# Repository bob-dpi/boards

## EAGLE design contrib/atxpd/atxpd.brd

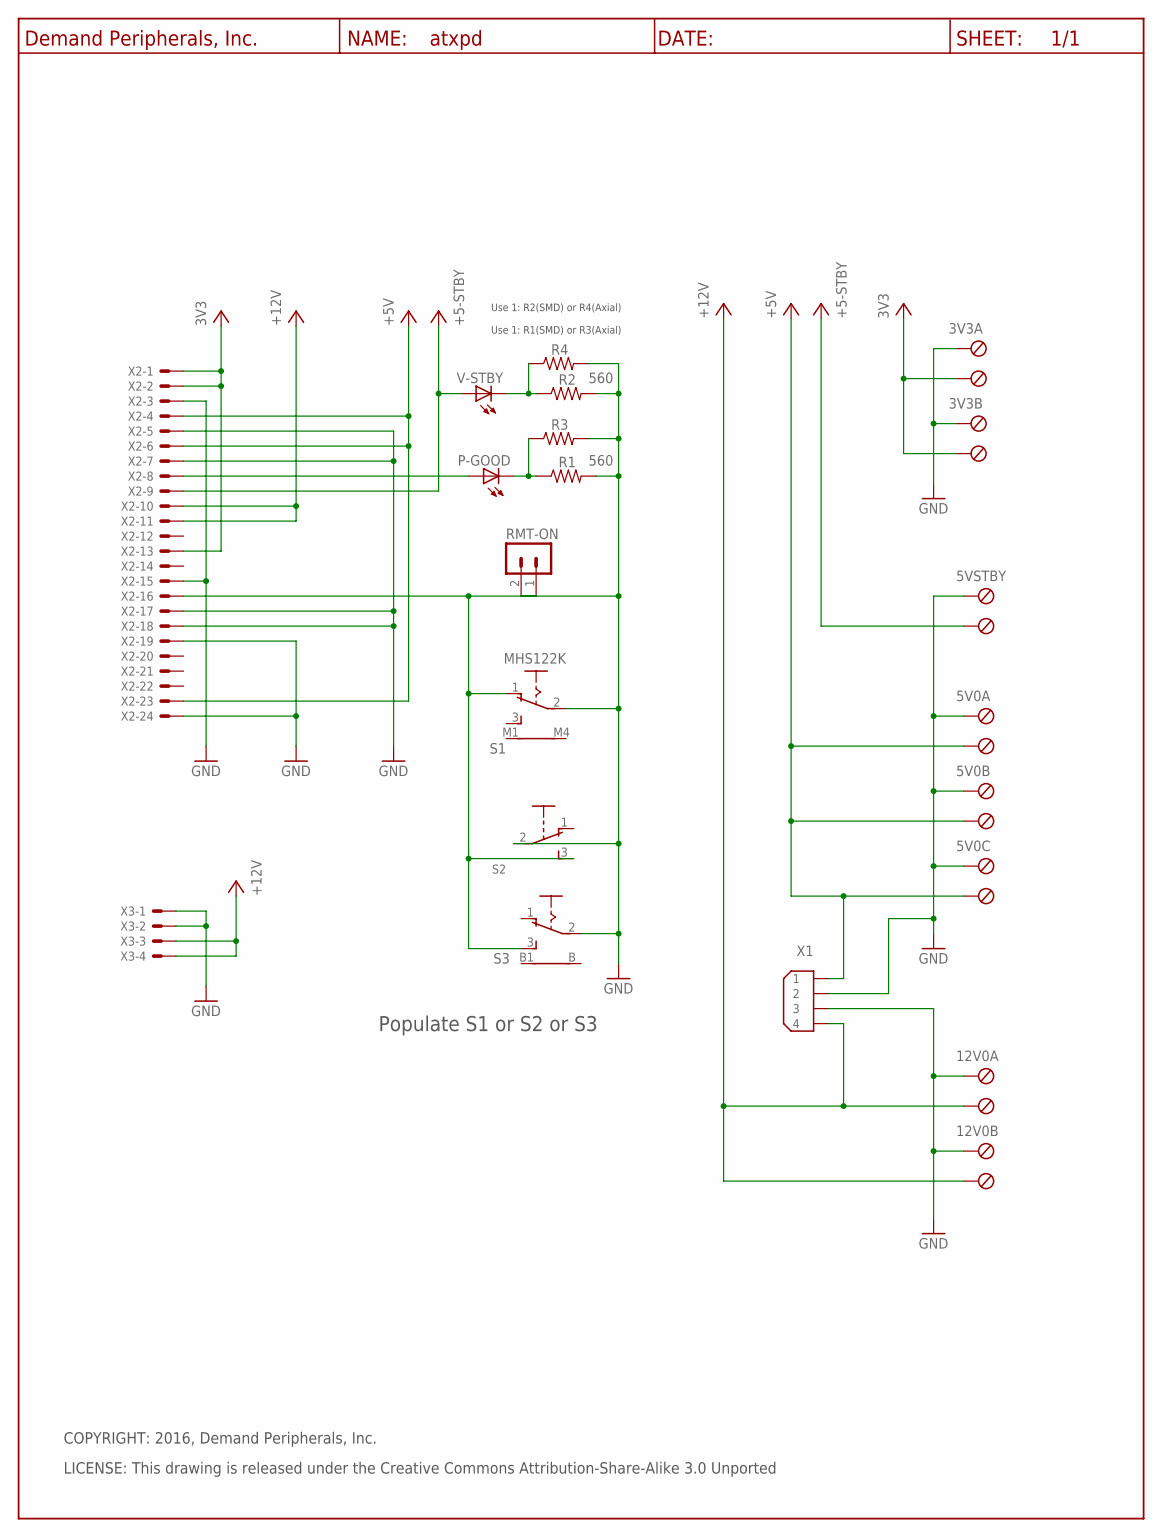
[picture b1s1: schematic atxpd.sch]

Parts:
3V3A, 3V3B, 5V0A, 5V0B, 5V0C, 5VSTBY, 12V0A, 12V0B: TBLK-5.08-X2
P-GOOD: 3mm_LED; LED5MM
R1, R2: 560; R0603
R3, R4: 560; R4TENTHS
RMT-ON: PinHdr254-2; HDR-2X1
S1: MHS122K
S2: TINYTOGGLE-SPDT-TH; SPDT-TENTHINCH
S3: Vert_SW(Option); TOGGLE_SPDT_PC
U$1: DP_FRAME_P; LETTER_P
V-STBY: 3mm_LED; LED5MM
X1: 9090-4V
X2: ATX_Std; 5566-24MOD
X3: ATX_Plus4; 5566-4MOD

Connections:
+3,3V: 3V3A.2 (KL1), 3V3B.2 (KL1), X2.1, X2.2, X2.13
+5V: 5V0A.2 (KL1), 5V0B.2 (KL1), 5V0C.2 (KL1), X1.1, X2.4, X2.6, X2.23
+5V/1: 5VSTBY.2 (KL1), V-STBY.A, X2.9
+5V/2: 12V0A.2 (KL1), 12V0B.2 (KL1), X1.4, X2.10, X2.11, X3.3, X3.4
GND: 3V3A.1 (KL), 3V3B.1 (KL), 5V0A.1 (KL), 5V0B.1 (KL), 5V0C.1 (KL), 5VSTBY.1 (KL), 12V0A.1 (KL), 12V0B.1 (KL), R1.2, R2.2, R3.2, R4.2, RMT-ON.2 (1), S1.2, S2.2, S3.2, X1.2, X1.3, X2.3, X2.5, X2.7, X2.15, X2.17, X2.18, X2.19, X2.24, X3.1, X3.2
unnamed: P-GOOD.A, X2.8
unnamed: P-GOOD.C, R1.1, R3.1
unnamed: R2.1, R4.1, V-STBY.C
unnamed: RMT-ON.1 (2), S1.1 (O), S2.3, S3.3 (S), X2.16

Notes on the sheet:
Use 1: R2(SMD) or R4(Axial)
Use 1: R1(SMD) or R3(Axial)
Populate S1 or S2 or S3
LICENSE: This drawing is released under the Creative Commons Attribution-Share-Alike 3.0 Unported
COPYRIGHT: 2016, Demand Peripherals, Inc.

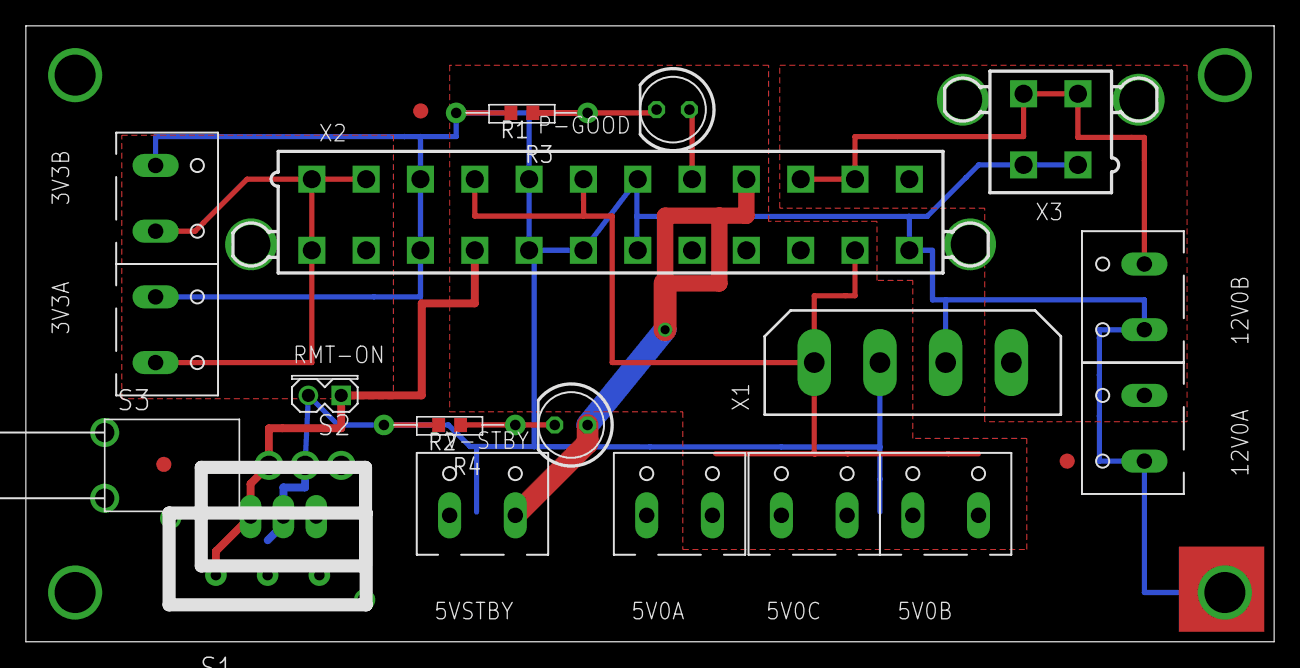
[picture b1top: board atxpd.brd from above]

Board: 2 copper layers, 96.5 x 47.6 mm, 25 parts (0 on the bottom side), 9 nets.

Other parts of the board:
U$9, U$10, U$11: FIDUCIAL

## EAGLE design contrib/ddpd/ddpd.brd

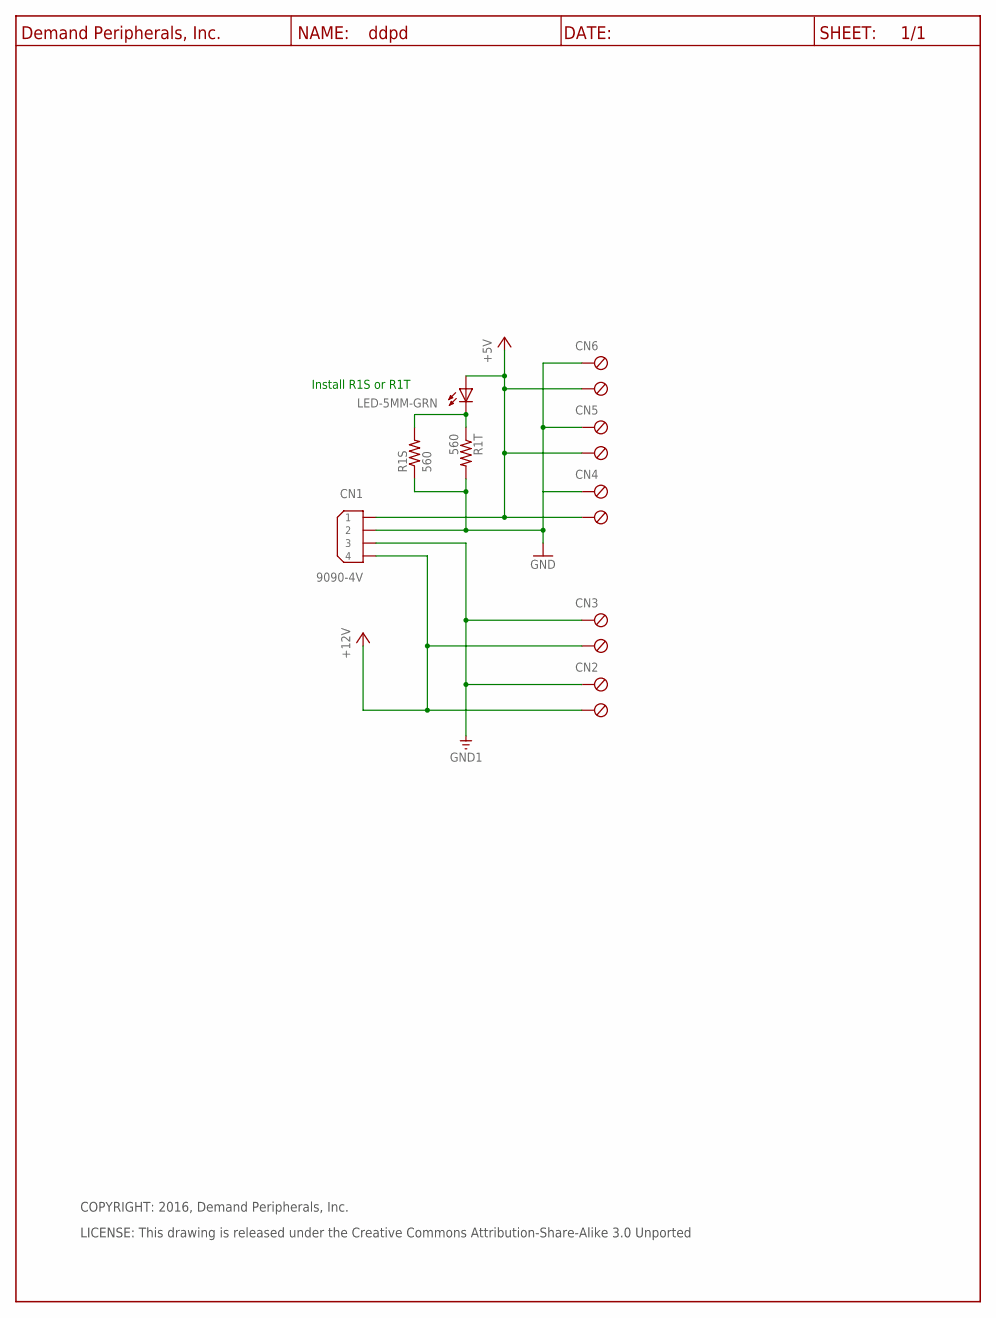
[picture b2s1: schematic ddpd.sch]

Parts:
+5V: LED-5MM-GRN; LED5MM
CN1: 9090-4V; 9090-4R
CN2, CN3, CN4, CN5, CN6: TBLK-5.08-X2
R1S: 560; R0603
R1T: 560; R4TENTHS
U$4: DP_FRAME_P; LETTER_P

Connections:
+5V: +5V.A, CN1.1, CN4.2 (KL1), CN5.2 (KL1), CN6.2 (KL1)
+5V/2: CN1.4, CN2.2 (KL1), CN3.2 (KL1)
GND: CN1.2, CN4.1 (KL), CN5.1 (KL), CN6.1 (KL), R1S.1, R1T.2
GND1: CN1.3, CN2.1 (KL), CN3.1 (KL)
unnamed: +5V.C, R1S.2, R1T.1

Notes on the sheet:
Install R1S or R1T
LICENSE: This drawing is released under the Creative Commons Attribution-Share-Alike 3.0 Unported
COPYRIGHT: 2016, Demand Peripherals, Inc.

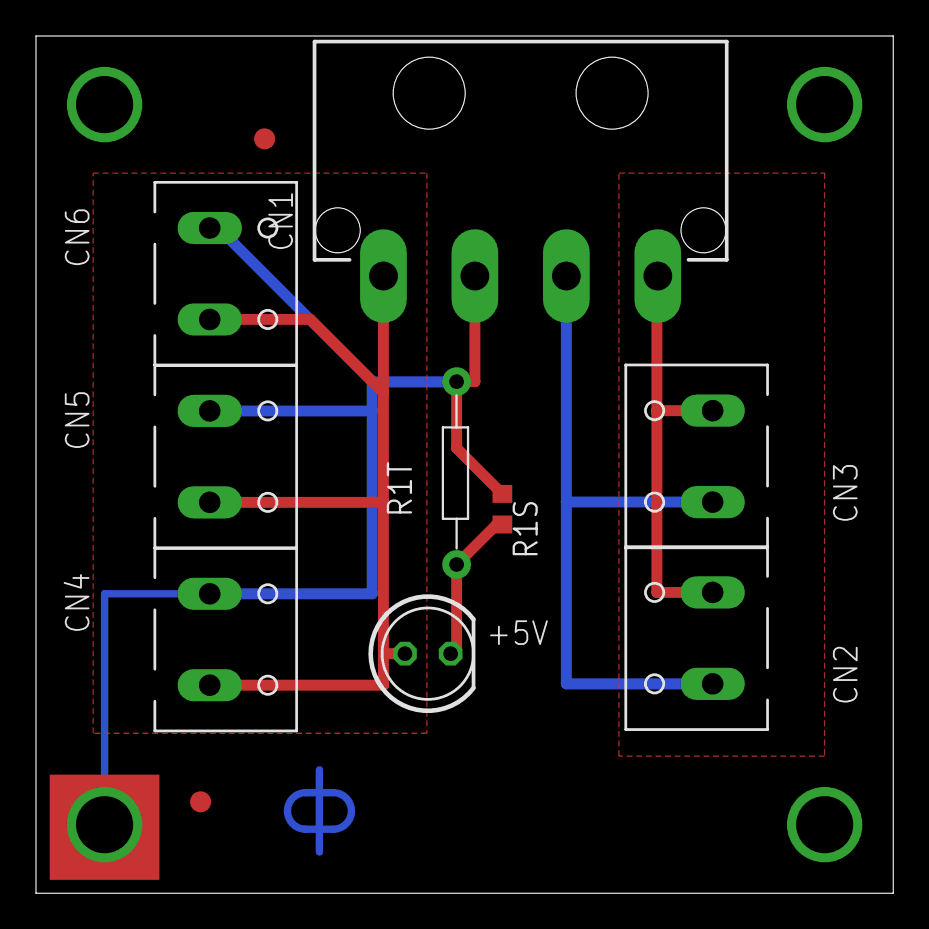
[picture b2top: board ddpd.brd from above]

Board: 2 copper layers, 47.6 x 47.6 mm, 13 parts (1 on the bottom side), 5 nets.

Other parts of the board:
U$1: DPI-1
U$2, U$3: FIDUCIAL

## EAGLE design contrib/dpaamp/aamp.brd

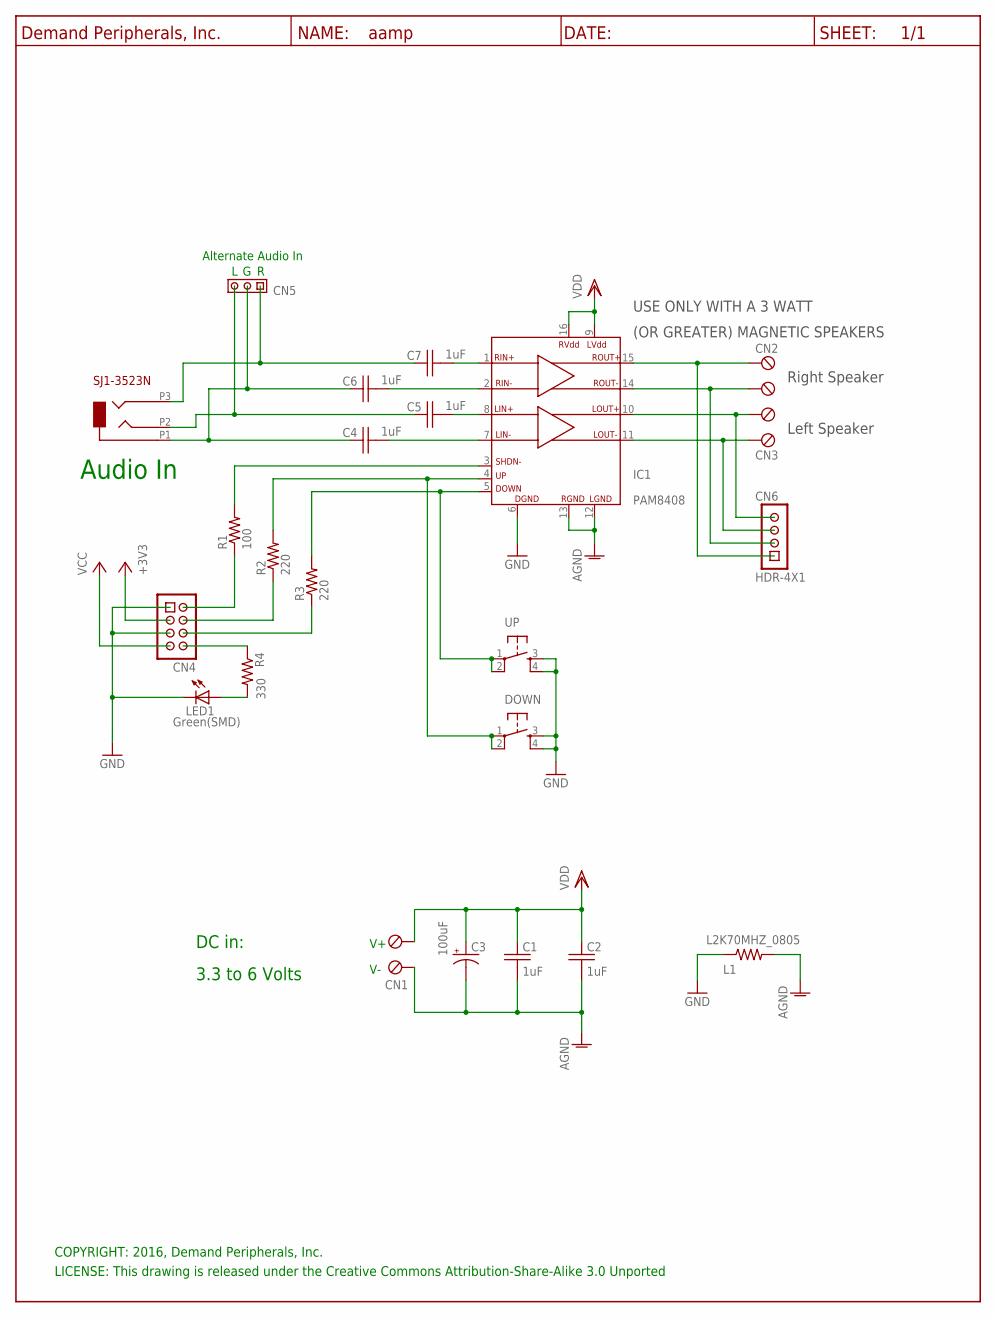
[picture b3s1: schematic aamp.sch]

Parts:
AUDIN: SJ1-3523N; CUI-SJ1-3523N
C1, C2, C4, C5, C6, C7: 1uF; C0603
C3: 100uF; E3.5-8
CN1, CN2, CN3: TBLK-5.08-X2
CN4: HDR-4X2-SHR; HDR-4X2
CN5: HDR-3X1
CN6: HDR-4X1
DOWN: DTSM-6
FRM1: DP_FRAME_P; P_FRAME
IC1: PAM8408; SO16
L1: L2K70MHZ_0805; R0805
LED1: Green(SMD); 0603
R1: 100; R0603
R2, R3: 220; R0603
R4: 330; R0603
UP: DTSM-6

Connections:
+3,3V: CN4.3
AGND: C1.2, C2.2, C3.-, CN1.1 (KL), IC1.12 (LGND), IC1.13 (RGND), L1.2
GND: CN4.1, CN4.5, DOWN.3, DOWN.4, IC1.6 (GND), L1.1, LED1.C, UP.3, UP.4
unnamed: AUDIN.P1 (1), C4.1, C6.1, CN5.2
unnamed: AUDIN.P2 (2), C5.1, CN5.3
unnamed: AUDIN.P3 (3), C7.1, CN5.1
unnamed: C7.2, IC1.1 (RIN+)
unnamed: CN4.8, R4.1
unnamed: C6.2, IC1.2 (RIN-)
unnamed: C5.2, IC1.8 (LIN+)
unnamed: C4.2, IC1.7 (LIN-)
unnamed: CN4.6, R3.1
unnamed: CN4.4, R2.1
unnamed: CN4.2, R1.1
unnamed: IC1.3 (SHDN-), R1.2
unnamed: LED1.A, R4.2
unnamed: DOWN.1, DOWN.2, IC1.4 (UP), R2.2
unnamed: IC1.5 (DOWN), R3.2, UP.1, UP.2
unnamed: CN3.2 (KL1), CN6.3, IC1.11 (LOUT-)
unnamed: CN3.1 (KL), CN6.4, IC1.10 (LOUT+)
unnamed: CN2.1 (KL), CN6.2, IC1.14 (ROUT-)
unnamed: CN2.2 (KL1), CN6.1, IC1.15 (ROUT+)
VCC: CN4.7
VDD: C1.1, C2.1, C3.+, CN1.2 (KL1), IC1.9 (LVDD), IC1.16 (RVDD)

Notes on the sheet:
DC in:
Audio In
3.3 to 6 Volts
USE ONLY WITH A 3 WATT
(OR GREATER) MAGNETIC SPEAKERS
COPYRIGHT: 2016, Demand Peripherals, Inc.
LICENSE: This drawing is released under the Creative Commons Attribution-Share-Alike 3.0 Unported
Left Speaker
Right Speaker
Alternate Audio In

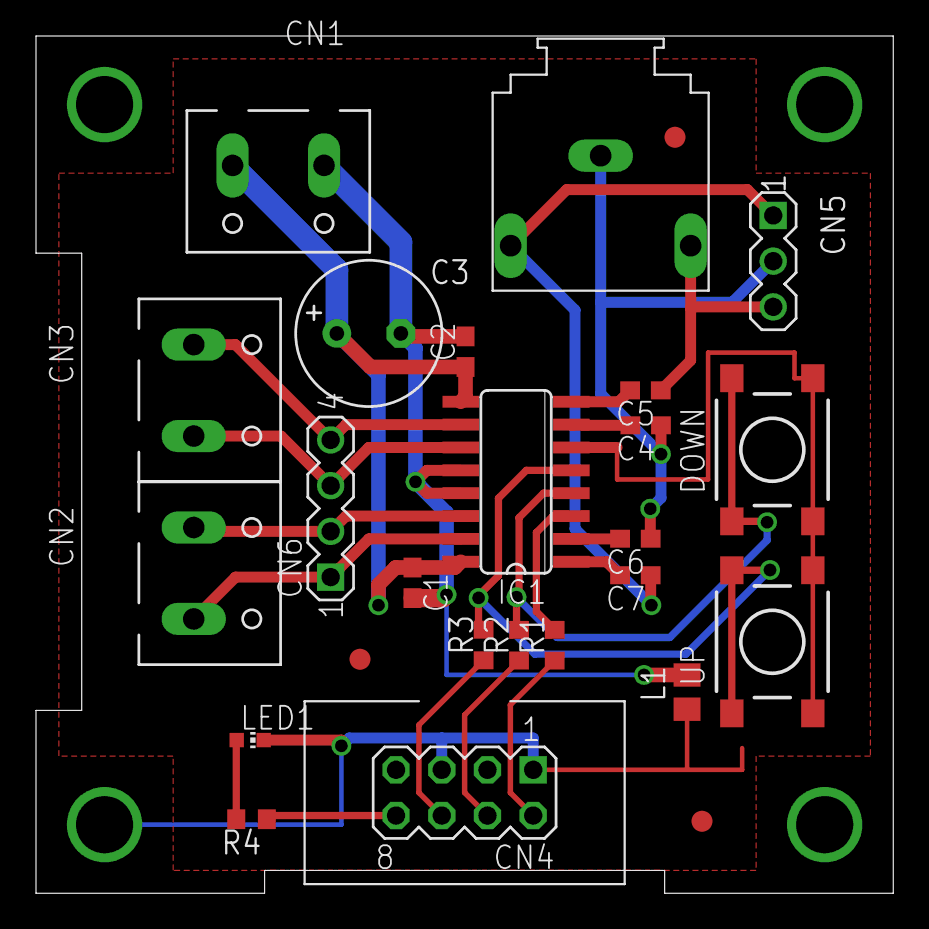
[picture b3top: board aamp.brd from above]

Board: 2 copper layers, 47.6 x 47.6 mm, 28 parts (1 on the bottom side), 22 nets.

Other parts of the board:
U$1: DPI-2
U$3, U$4, U$6: FIDUCIAL

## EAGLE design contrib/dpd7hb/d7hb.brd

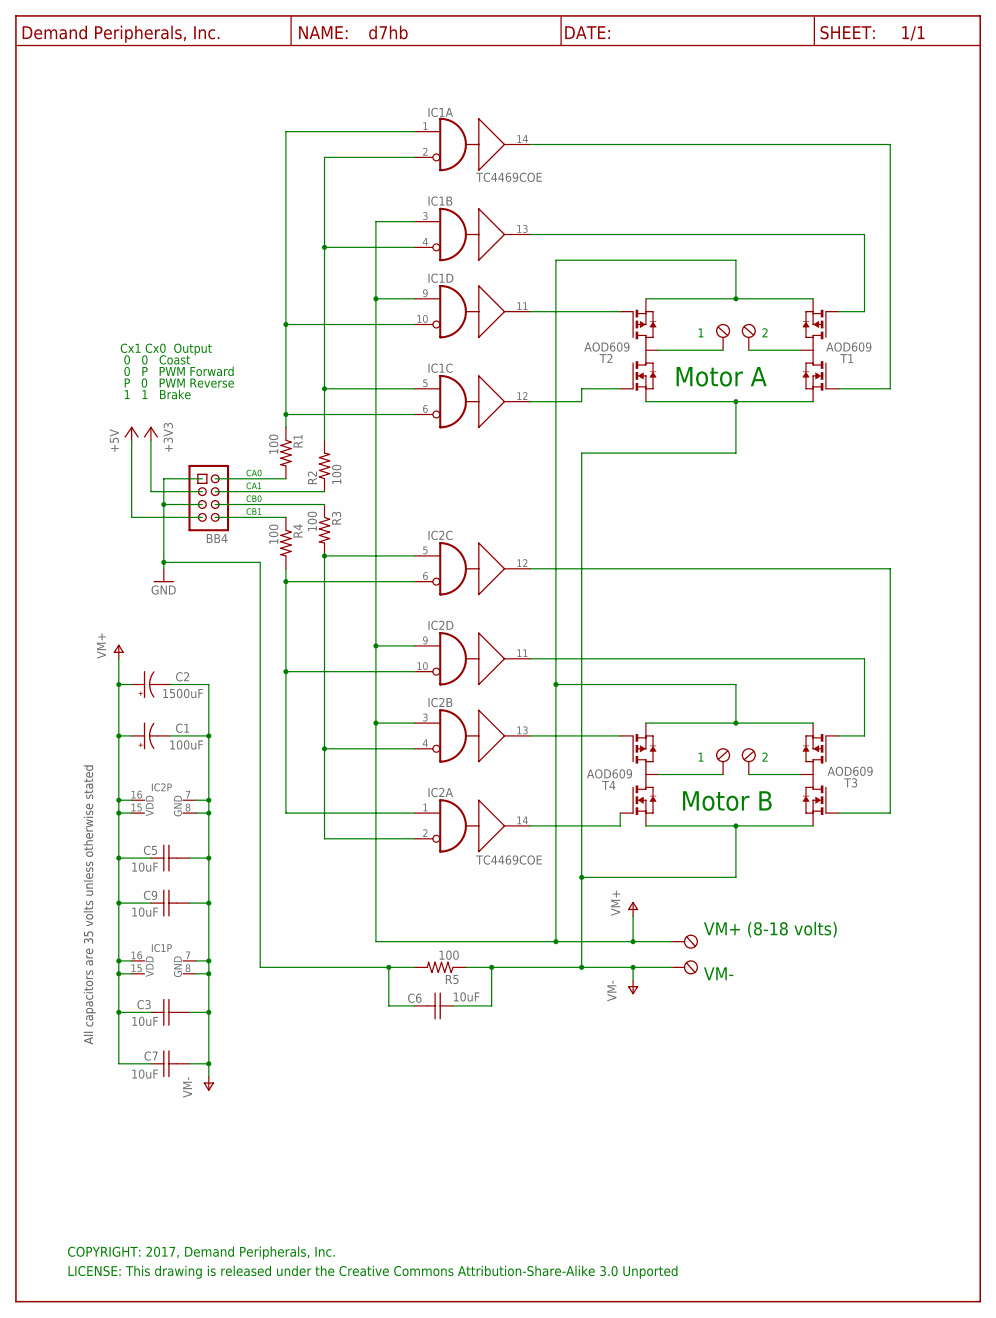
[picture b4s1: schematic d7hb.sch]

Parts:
BB4: BB_CON; HDR-4X2
C1: 100uF; E3.5-8
C2: 1500uF; E7,5-16
C3, C5, C6, C7, C9: 10uF; C0805
CN1, CN2, CN3: OSTTC022162; TBLK-5.08-X2
IC1, IC2: TC4469COE; SO-16DW
R1, R2, R3, R4, R5: 100; R0603
T1, T2, T3, T4: AOD609; TO252-41
U$1: DP_FRAME_P; LETTER_P

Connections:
+3V3: BB4.3
GND: BB4.1, BB4.5, C6.2, R5.2
unnamed: IC1.12 (Y), T2.2 (G1N)
unnamed: IC1.11 (Y), T2.5 (G2P)
unnamed: IC1.13 (Y), T1.5 (G2P)
unnamed: IC1.14 (Y), T1.2 (G1N)
unnamed: IC2.13 (Y), T4.5 (G2P)
unnamed: BB4.8, R4.1
unnamed: IC2.14 (Y), T4.2 (G1N)
unnamed: IC2.11 (Y), T3.5 (G2P)
unnamed: BB4.2, R1.2
unnamed: IC2.12 (Y), T3.2 (G1N)
unnamed: BB4.4, R2.1
unnamed: IC1.1 (A), IC1.6 (B), IC1.10 (B), R1.1
unnamed: IC1.2 (B), IC1.4 (B), IC1.5 (A), R2.2
unnamed: BB4.6, R3.1
unnamed: IC2.1 (A), IC2.6 (B), IC2.10 (B), R4.2
unnamed: IC2.2 (B), IC2.4 (B), IC2.5 (A), R3.2
unnamed: CN3.1 (KL), T2.CASE (D12)
unnamed: CN3.2 (KL1), T1.CASE (D12)
unnamed: CN2.2 (KL1), T4.CASE (D12)
unnamed: CN2.1 (KL), T3.CASE (D12)
V+: C1.+, C2.+, C3.1, C5.1, C7.1, C9.1, CN1.2 (KL1), IC1.3 (A), IC1.9 (A), IC1.15 (VDD), IC1.16 (VDD), IC2.3 (A), IC2.9 (A), IC2.15 (VDD), IC2.16 (VDD), T1.4 (S2P), T2.4 (S2P), T3.4 (S2P), T4.4 (S2P)
V-: C1.-, C2.-, C3.2, C5.2, C6.1, C7.2, C9.2, CN1.1 (KL), IC1.7 (GND), IC1.8 (GND), IC2.7 (GND), IC2.8 (GND), R5.1, T1.1 (S1N), T2.1 (S1N), T3.1 (S1N), T4.1 (S1N)
VCC: BB4.7

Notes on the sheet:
Motor A
VM+ (8-18 volts)
VM-
Motor B
CA0
CA1
CB0
CB1
Cx1 Cx0 Output
0 0 Coast
0 P PWM Forward
P 0 PWM Reverse
1 1 Brake
All capacitors are 35 volts unless otherwise stated
COPYRIGHT: 2017, Demand Peripherals, Inc.
LICENSE: This drawing is released under the Creative Commons Attribution-Share-Alike 3.0 Unported

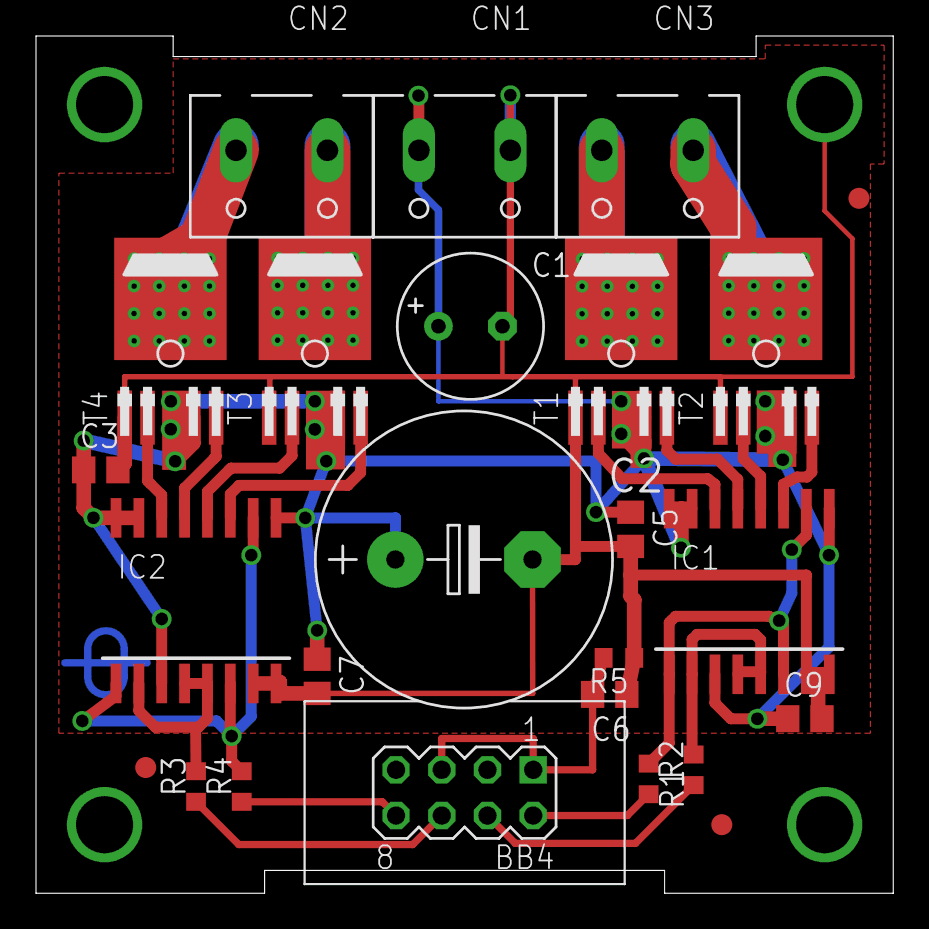
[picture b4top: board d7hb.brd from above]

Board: 2 copper layers, 47.6 x 47.6 mm, 27 parts (1 on the bottom side), 23 nets.

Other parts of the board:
U$2, U$3, U$4: FIDUCIAL
U$5: DPI-1

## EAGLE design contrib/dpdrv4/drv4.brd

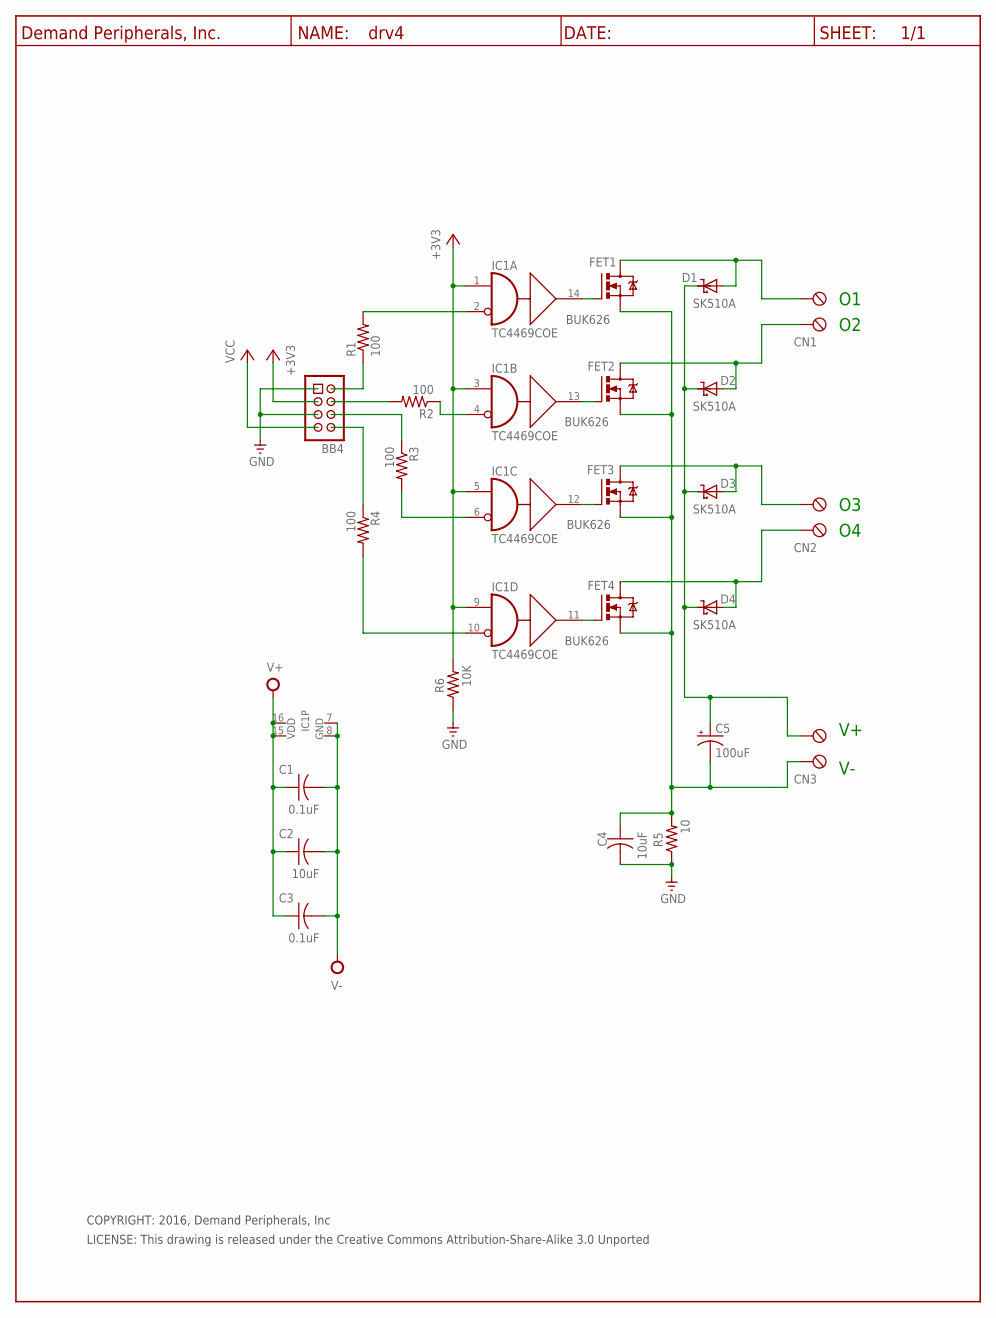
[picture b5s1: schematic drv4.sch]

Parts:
BB4: Keyed_Pin_Header_4x2(0.1"x0.1"); HDR-4X2
C1, C3: 0.1uF; C0603
C2, C4: 10uF; C0805
C5: 100uF; E3.5-8
CN1, CN2, CN3: TBLK-5.08-X2
D1, D2, D3, D4: SK510A; SMA
FET1, FET2, FET3, FET4: BUK626; DPACK_TO-252
IC1: TC4469COE; SO-16DW
R1, R2, R3, R4: 100; R0603
R5: 10; R0603
R6: 10K; R0603
U$1: DP_FRAME_P; P_FRAME

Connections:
+3V3: BB4.3, IC1.1 (A), IC1.3 (A), IC1.5 (A), IC1.9 (A), R6.2
GND: BB4.1, BB4.5, C4.2, R5.1, R6.1
unnamed: IC1.10 (B), R4.2
unnamed: IC1.2 (B), R1.2
unnamed: IC1.4 (B), R2.1
unnamed: FET1.1 (G), IC1.14 (Y)
unnamed: FET2.1 (G), IC1.13 (Y)
unnamed: FET3.1 (G), IC1.12 (Y)
unnamed: FET4.1 (G), IC1.11 (Y)
unnamed: BB4.2, R1.1
unnamed: BB4.4, R2.2
unnamed: BB4.6, R3.1
unnamed: IC1.6 (B), R3.2
unnamed: BB4.8, R4.1
O1: CN2.1 (KL), D4.A, FET4.4 (D)
O2: CN2.2 (KL1), D3.A, FET3.4 (D)
O3: CN1.1 (KL), D2.A, FET2.4 (D)
O4: CN1.2 (KL1), D1.A, FET1.4 (D)
V+: C1.1, C2.1, C3.1, C5.+, CN3.2 (KL1), D1.C (CC), D2.C (CC), D3.C (CC), D4.C (CC), IC1.15 (VDD), IC1.16 (VDD)
V-: C1.2, C2.2, C3.2, C4.1, C5.-, CN3.1 (KL), FET1.3 (S), FET2.3 (S), FET3.3 (S), FET4.3 (S), IC1.7 (GND), IC1.8 (GND), R5.2
VCC: BB4.7

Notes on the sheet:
COPYRIGHT: 2016, Demand Peripherals, Inc
LICENSE: This drawing is released under the Creative Commons Attribution-Share-Alike 3.0 Unported

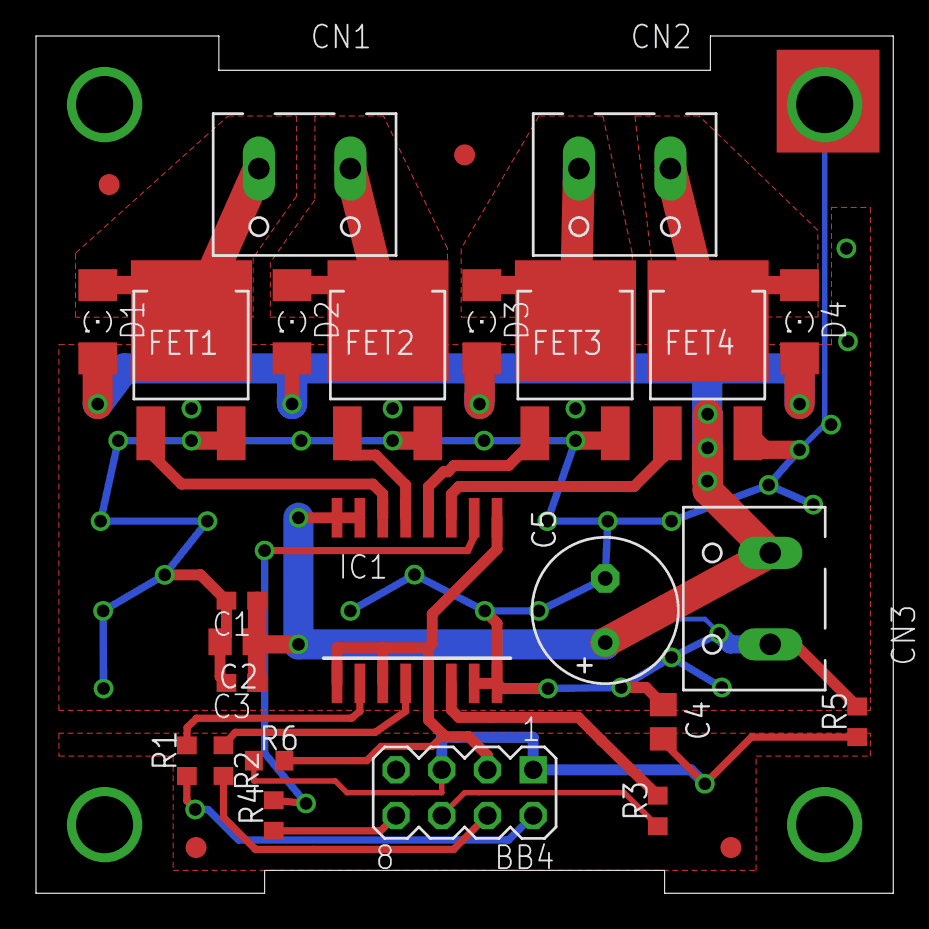
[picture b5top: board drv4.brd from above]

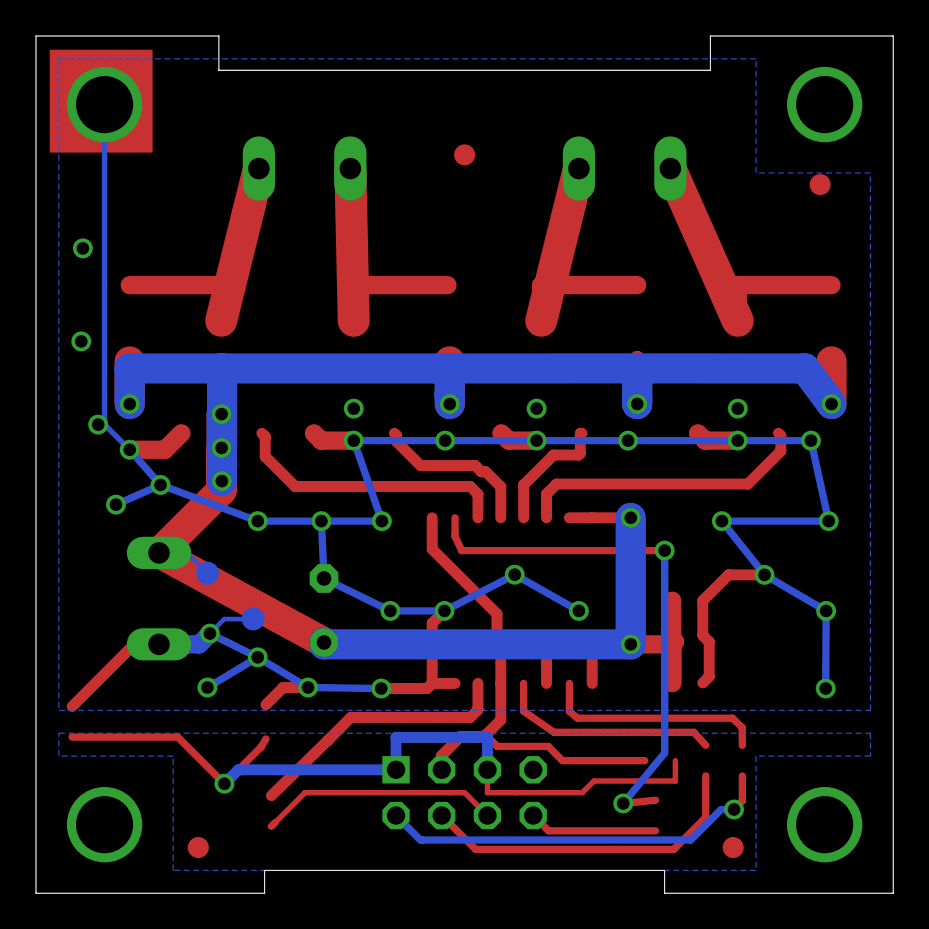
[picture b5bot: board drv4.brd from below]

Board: 2 copper layers, 47.6 x 47.6 mm, 32 parts (3 on the bottom side), 20 nets.

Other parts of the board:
E$6: TEST-POINT
U$2, U$3, U$4, U$5: FIDUCIAL
U$7: DPI-2
V-: TEST-POINT

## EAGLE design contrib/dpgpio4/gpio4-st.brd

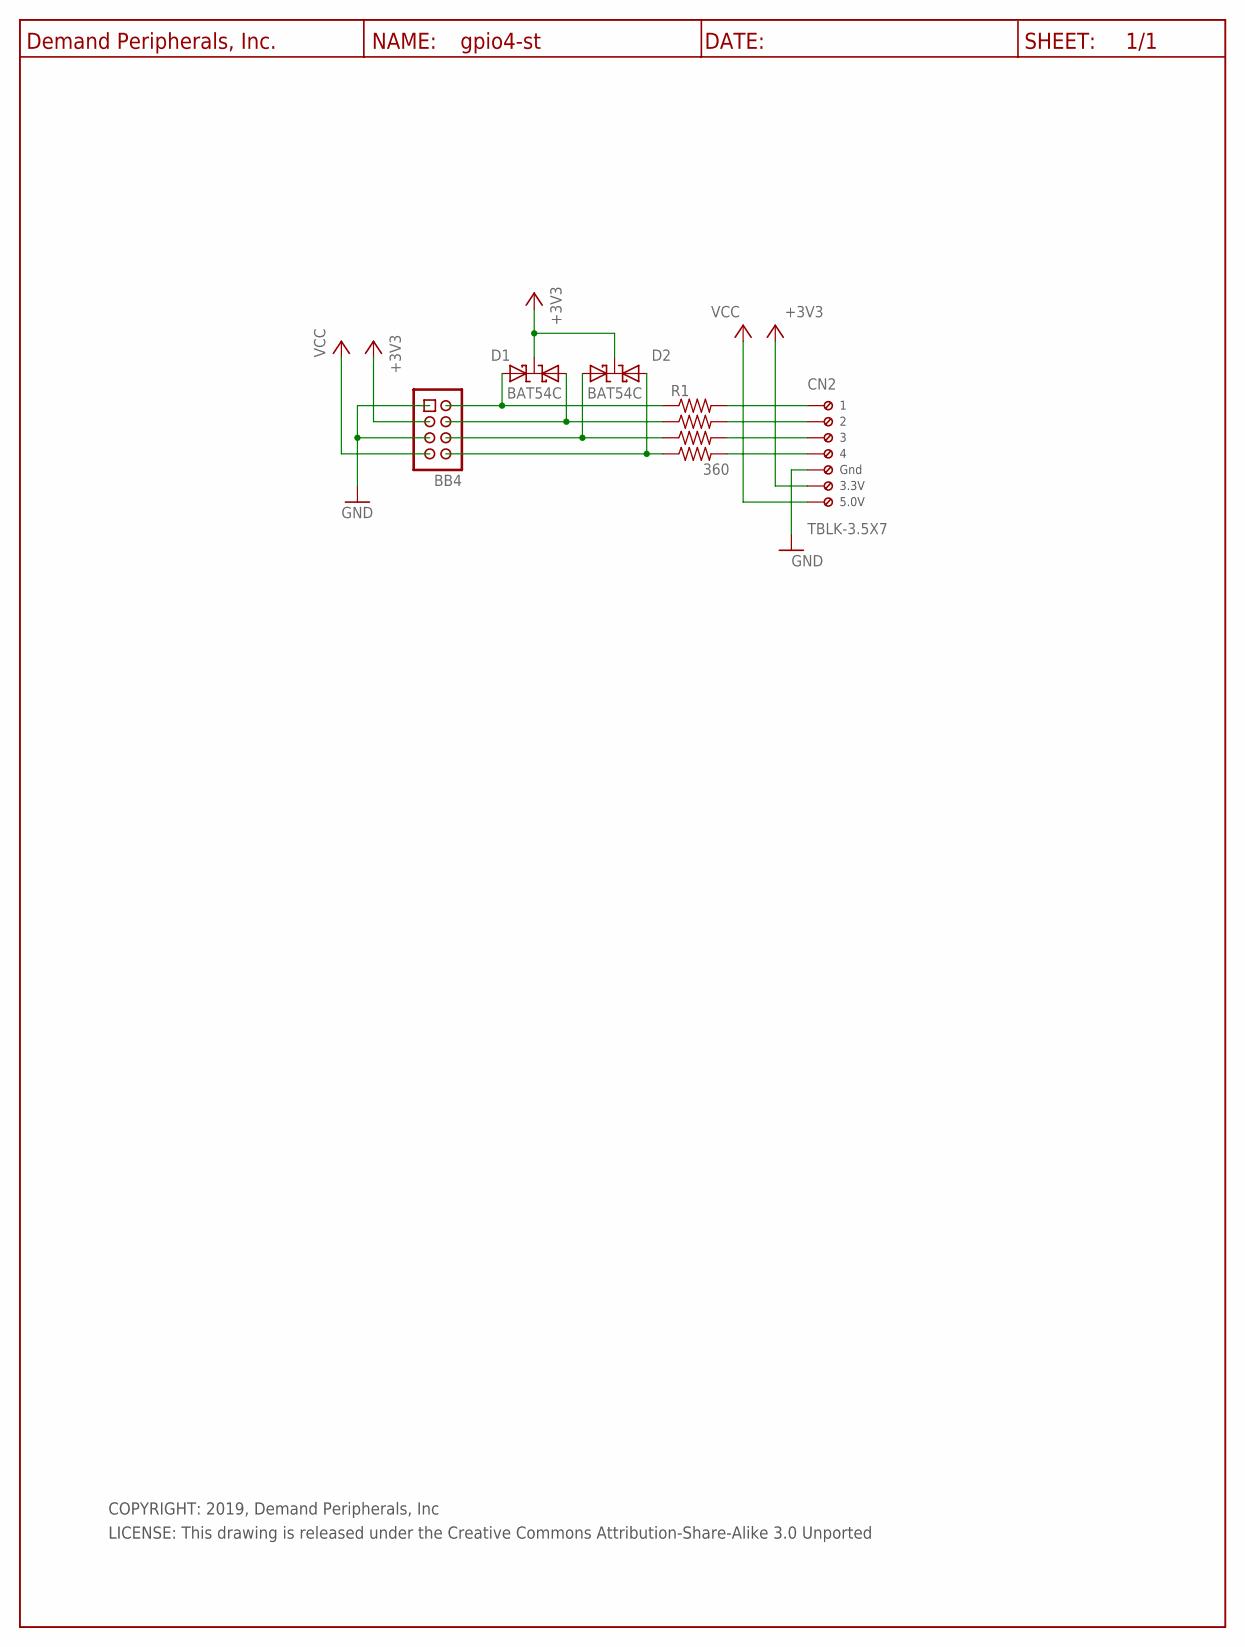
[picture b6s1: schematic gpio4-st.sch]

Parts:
BB4: BB_CON; HDR-4X2
CN2: TBLK-3.5X7
D1, D2: BAT54C; SOT23
R1, R2, R3, R4: 360; R0603
U$1: DP_FRAME_P; P_FRAME

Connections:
+3V3: BB4.3, CN2.6 (KL5), D1.3 (CC), D2.3 (CC)
GND: BB4.1, BB4.5, CN2.5 (KL4)
unnamed: CN2.1 (KL), R1.2
unnamed: CN2.2 (KL1), R2.2
unnamed: CN2.3 (KL2), R3.2
unnamed: CN2.4 (KL3), R4.2
unnamed: BB4.2, D1.1 (A1), R1.1
unnamed: BB4.4, D1.2 (A), R2.1
unnamed: BB4.6, D2.1 (A1), R3.1
unnamed: BB4.8, D2.2 (A), R4.1
VCC: BB4.7, CN2.7 (KL6)

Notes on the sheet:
COPYRIGHT: 2019, Demand Peripherals, Inc
LICENSE: This drawing is released under the Creative Commons Attribution-Share-Alike 3.0 Unported
Gnd
3.3V
5.0V

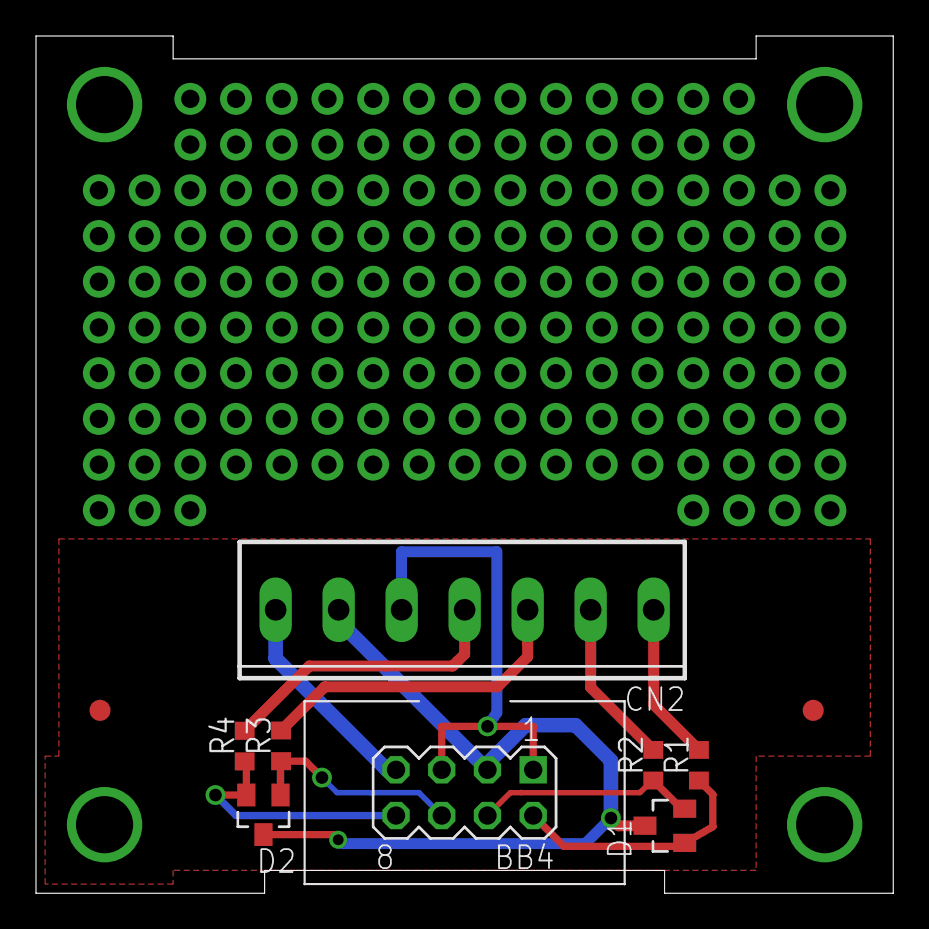
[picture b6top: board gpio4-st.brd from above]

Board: 2 copper layers, 47.6 x 47.6 mm, 12 parts (1 on the bottom side), 11 nets.

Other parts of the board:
U$2: DPI-2
U$3, U$8: FIDUCIAL

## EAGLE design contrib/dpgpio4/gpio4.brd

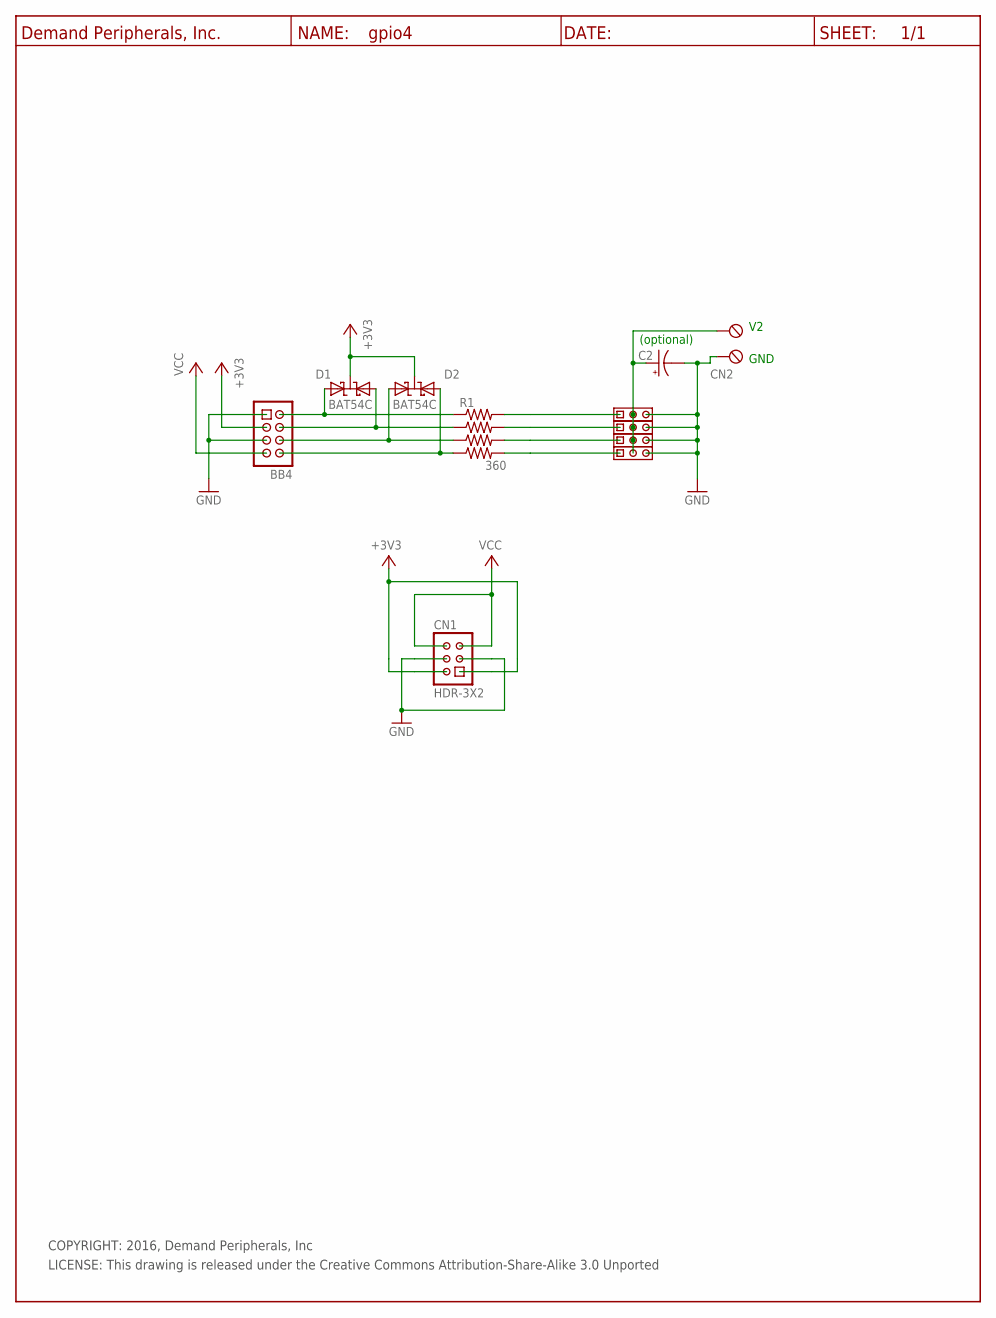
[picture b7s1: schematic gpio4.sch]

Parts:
BB4: BB_CON; HDR-4X2
C2: 100uF; E3.5-8
CN1: HDR-3X2
CN2: TBLK-5.08-X2
D1, D2: BAT54C; SOT23
R1, R2, R3, R4: 360; R0603
U$1: DP_FRAME_P; P_FRAME
U$5, U$6, U$7, U$9: HDR-3X1

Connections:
+3V3: BB4.3, CN1.1, CN1.2, D1.3 (CC), D2.3 (CC)
GND: BB4.1, BB4.5, C2.-, CN1.3, CN1.4, CN2.1 (KL), U$5.3, U$6.3, U$7.3, U$9.3
unnamed: R1.2, U$5.1
unnamed: R2.2, U$6.1
unnamed: R3.2, U$7.1
unnamed: R4.2, U$9.1
unnamed: BB4.2, D1.1 (A1), R1.1
unnamed: BB4.4, D1.2 (A), R2.1
unnamed: BB4.6, D2.1 (A1), R3.1
unnamed: BB4.8, D2.2 (A), R4.1
unnamed: C2.+, CN2.2 (KL1), U$5.2, U$6.2, U$7.2, U$9.2
VCC: BB4.7, CN1.5, CN1.6

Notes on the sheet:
GND
(optional)
COPYRIGHT: 2016, Demand Peripherals, Inc
LICENSE: This drawing is released under the Creative Commons Attribution-Share-Alike 3.0 Unported

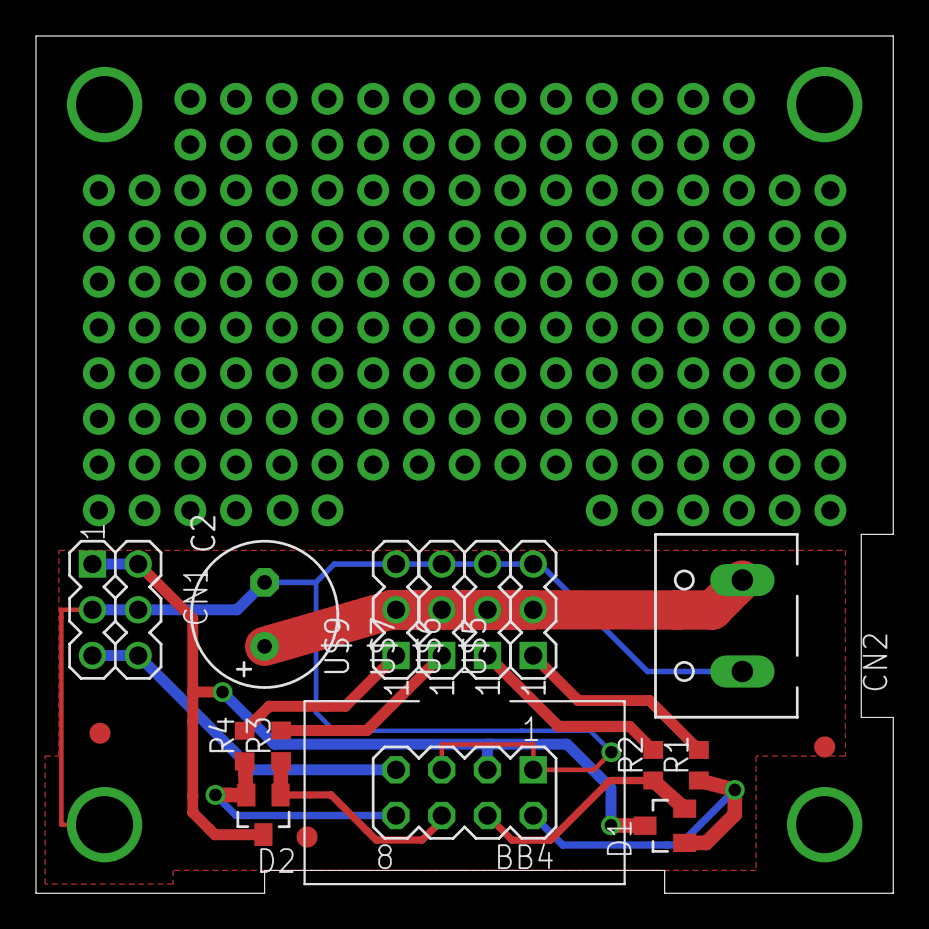
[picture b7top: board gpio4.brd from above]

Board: 2 copper layers, 47.6 x 47.6 mm, 19 parts (1 on the bottom side), 12 nets.

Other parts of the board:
U$2, U$3, U$8: FIDUCIAL
U$4: DPI-2

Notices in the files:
contrib/atxpd/atxpd.brd:
(C) 2017, Demand Peripherals, Inc.
contrib/dpaamp/aamp.brd:
(C) 2019, Demand Peripherals, Inc.
